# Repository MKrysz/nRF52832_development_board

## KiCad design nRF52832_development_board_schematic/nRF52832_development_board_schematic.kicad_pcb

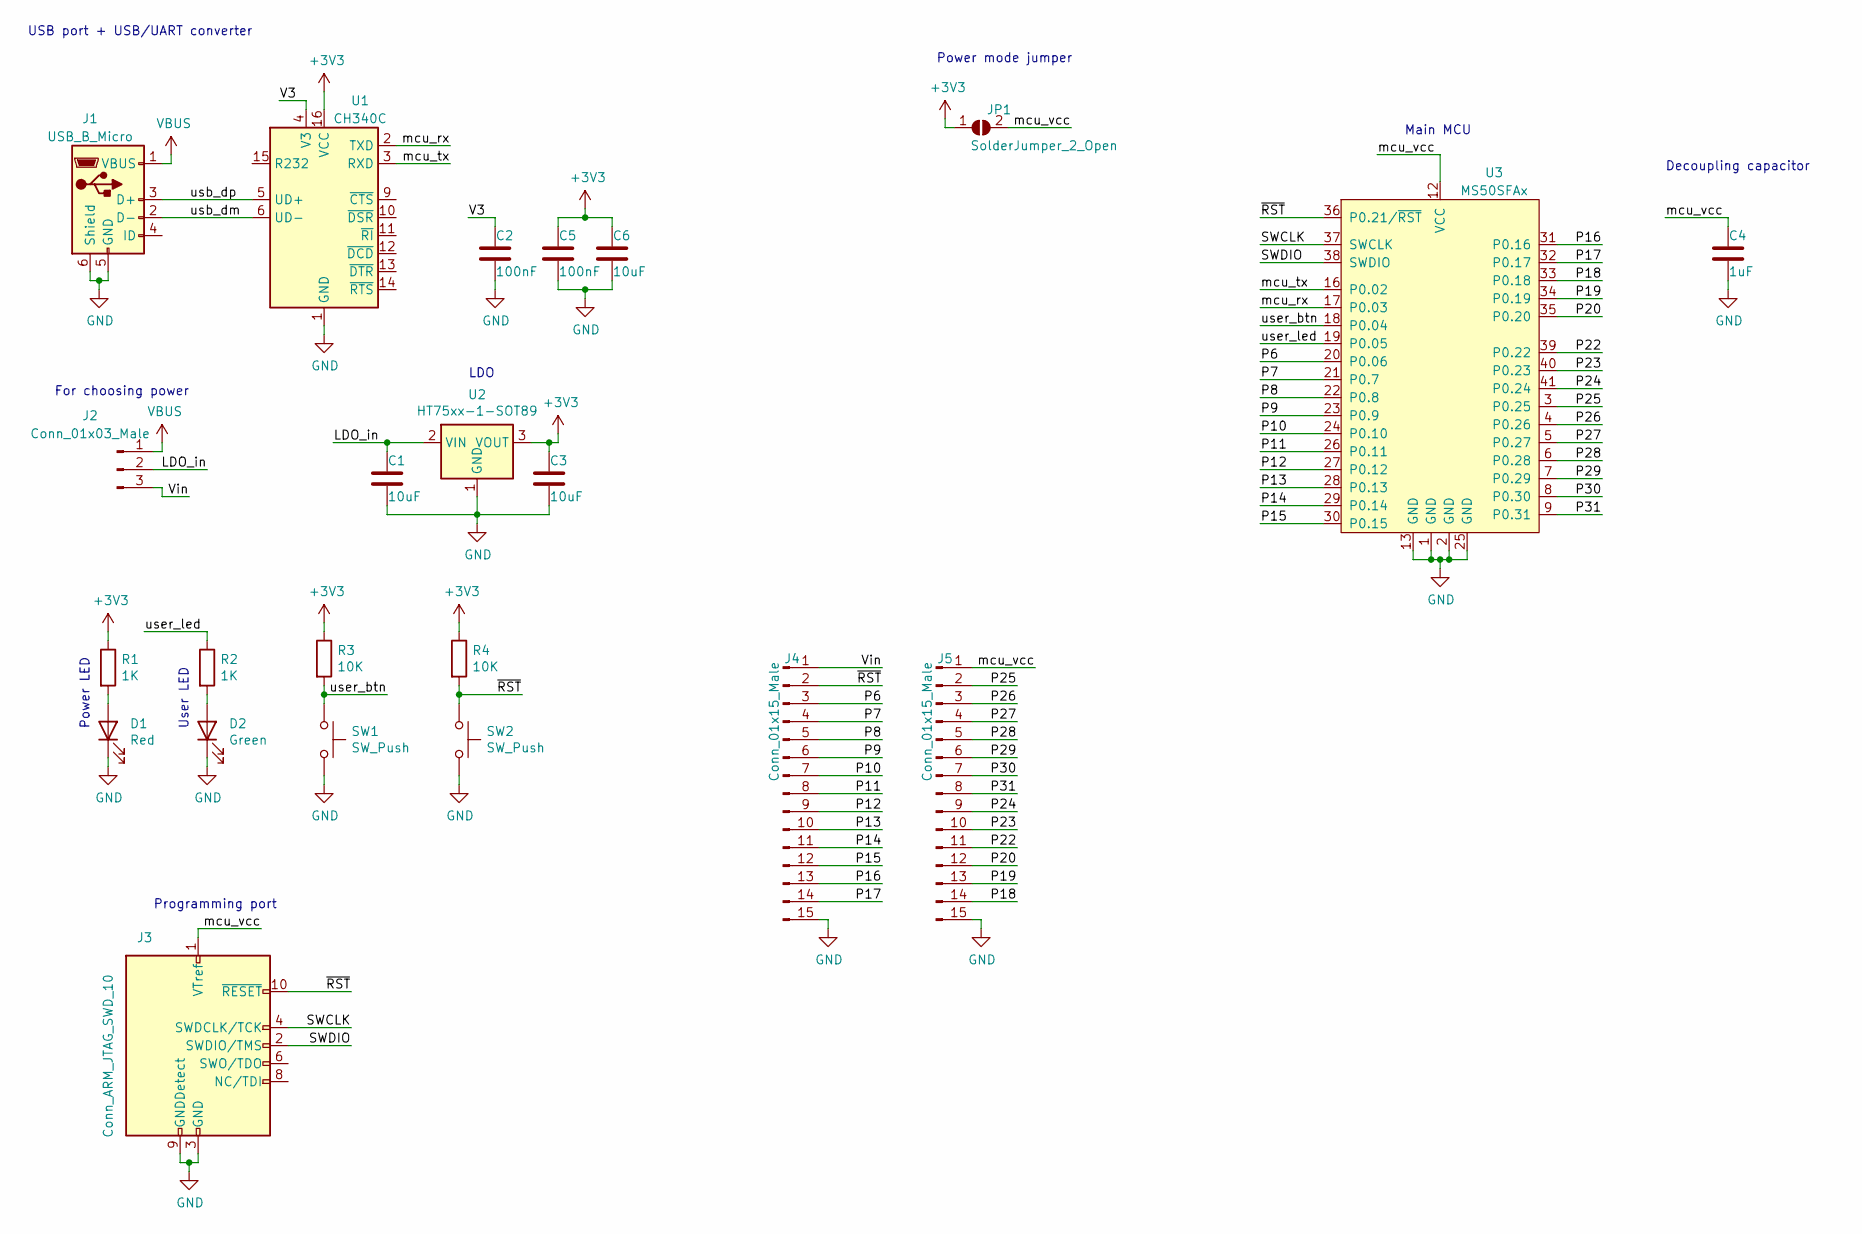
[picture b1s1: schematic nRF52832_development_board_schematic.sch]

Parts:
C1, C3, C6: 10uF; C_1206_3216Metric_Pad1.33x1.80mm_HandSolder
C2, C5: 100nF; C_1206_3216Metric_Pad1.33x1.80mm_HandSolder
C4: 1uF; C_1206_3216Metric_Pad1.33x1.80mm_HandSolder
D1: Red; LED_1206_3216Metric_Pad1.42x1.75mm_HandSolder
D2: Green; LED_1206_3216Metric_Pad1.42x1.75mm_HandSolder
J1: USB_B_Micro; USB_Micro-AB_Molex_47590-0001
J2: Conn_01x03_Male; PinHeader_1x03_P2.54mm_Vertical
J3: Conn_ARM_JTAG_SWD_10; IDC-Header_2x05_P2.54mm_Vertical
J4, J5: Conn_01x15_Male; PinHeader_1x15_P2.54mm_Vertical
JP1: SolderJumper_2_Open; SolderJumper-2_P1.3mm_Open_RoundedPad1.0x1.5mm
R1, R2: 1K; R_1206_3216Metric_Pad1.30x1.75mm_HandSolder
R3, R4: 10K; R_1206_3216Metric_Pad1.30x1.75mm_HandSolder
SW1, SW2: SW_Push; TSB008
U1: CH340C; SOIC-16_3.9x9.9mm_P1.27mm
U2: HT75xx-1-SOT89; SOT-89-3
U3: MS50SFAx; MS50SFB

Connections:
+3V3: C3.1, C5.1, C6.1, JP1.1 (A), R1.1, R3.1, R4.1, U1.16 (VCC), U2.3 (VOUT)
/LDO_in: C1.1, J2.2, U2.2 (VIN)
/P6: J4.3, U3.20 (P0.06)
/P7: J4.4, U3.21 (P0.7)
/P8: J4.5, U3.22 (P0.8)
/P9: J4.6, U3.23 (P0.9)
/P10: J4.7, U3.24 (P0.10)
/P11: J4.8, U3.26 (P0.11)
/P12: J4.9, U3.27 (P0.12)
/P13: J4.10, U3.28 (P0.13)
/P14: J4.11, U3.29 (P0.14)
/P15: J4.12, U3.30 (P0.15)
/P16: J4.13, U3.31 (P0.16)
/P17: J4.14, U3.32 (P0.17)
/P18: J5.14, U3.33 (P0.18)
/P19: J5.13, U3.34 (P0.19)
/P20: J5.12, U3.35 (P0.20)
/P22: J5.11, U3.39 (P0.22)
/P23: J5.10, U3.40 (P0.23)
/P24: J5.9, U3.41 (P0.24)
/P25: J5.2, U3.3 (P0.25)
/P26: J5.3, U3.4 (P0.26)
/P27: J5.4, U3.5 (P0.27)
/P28: J5.5, U3.6 (P0.28)
/P29: J5.6, U3.7 (P0.29)
/P30: J5.7, U3.8 (P0.30)
/P31: J5.8, U3.9 (P0.31)
/SWCLK: J3.4 (SWDCLK/TCK), U3.37 (SWCLK)
/SWDIO: J3.2 (SWDIO/TMS), U3.38 (SWDIO)
/V3: C2.1, U1.4 (V3)
/Vin: J2.3, J4.1
/mcu_rx: U1.2 (TXD), U3.17 (P0.03)
/mcu_tx: U1.3 (RXD), U3.16 (P0.02)
/mcu_vcc: C4.1, J3.1 (VTref), J5.1, JP1.2 (B), U3.12 (VCC)
/usb_dm: J1.2 (D-), U1.6 (UD-)
/usb_dp: J1.3 (D+), U1.5 (UD+)
/user_btn: R3.2, SW1.1, U3.18 (P0.04)
/user_led: R2.1, U3.19 (P0.05)
/~RST: J3.10 (~RESET~), J4.2, R4.2, SW2.1, U3.36 (P0.21/~RST)
GND: C1.2, C2.2, C3.2, C4.2, C5.2, C6.2, D1.1 (K), D2.1 (K), J1.5 (GND), J1.6 (Shield), J3.3 (GND), J3.5 (GND), J3.9 (GNDDetect), J4.15, J5.15, SW1.2, SW2.2, U1.1 (GND), U2.1 (GND), U3.1 (GND), U3.2 (GND), U3.13 (GND), U3.25 (GND)
unnamed: D1.2 (A), R1.2
unnamed: D2.2 (A), R2.2
VBUS: J1.1 (VBUS), J2.1

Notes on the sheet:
Main MCU
Decoupling capacitor
For choosing power
Power mode jumper
LDO
USB port + USB/UART converter
Power LED
User LED
Programming port

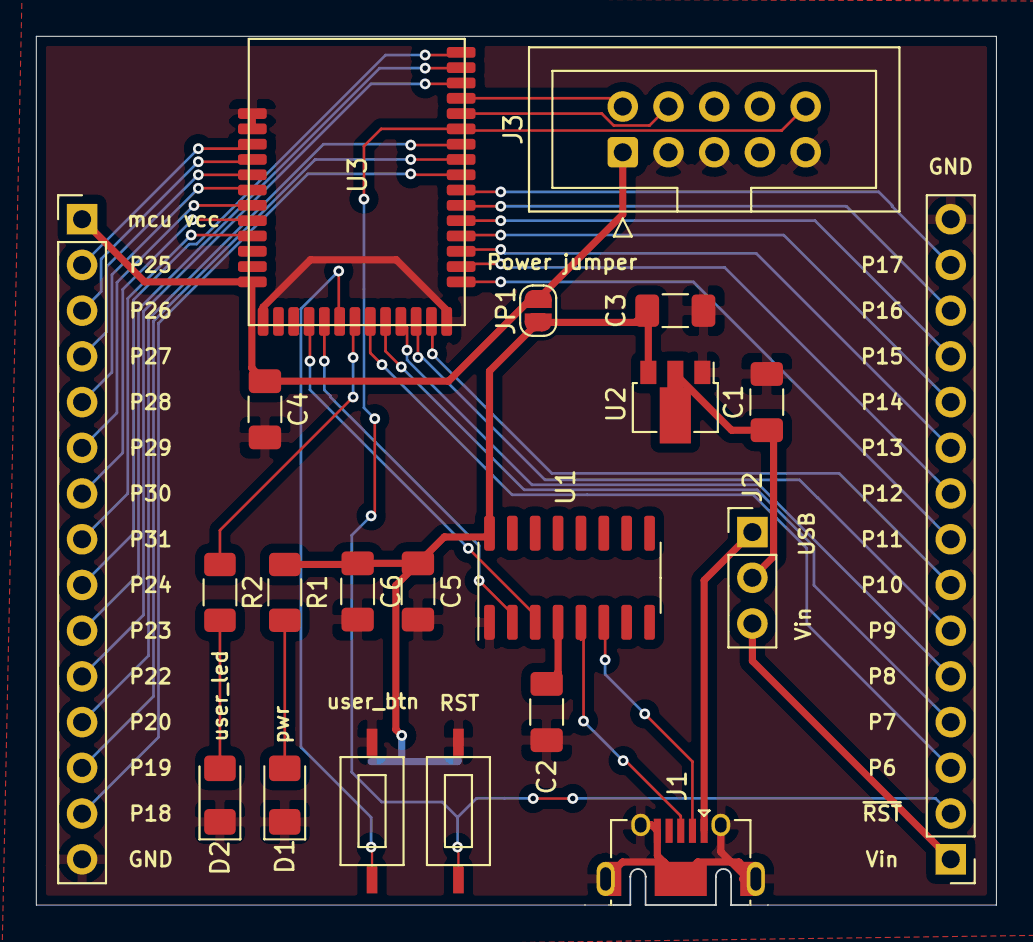
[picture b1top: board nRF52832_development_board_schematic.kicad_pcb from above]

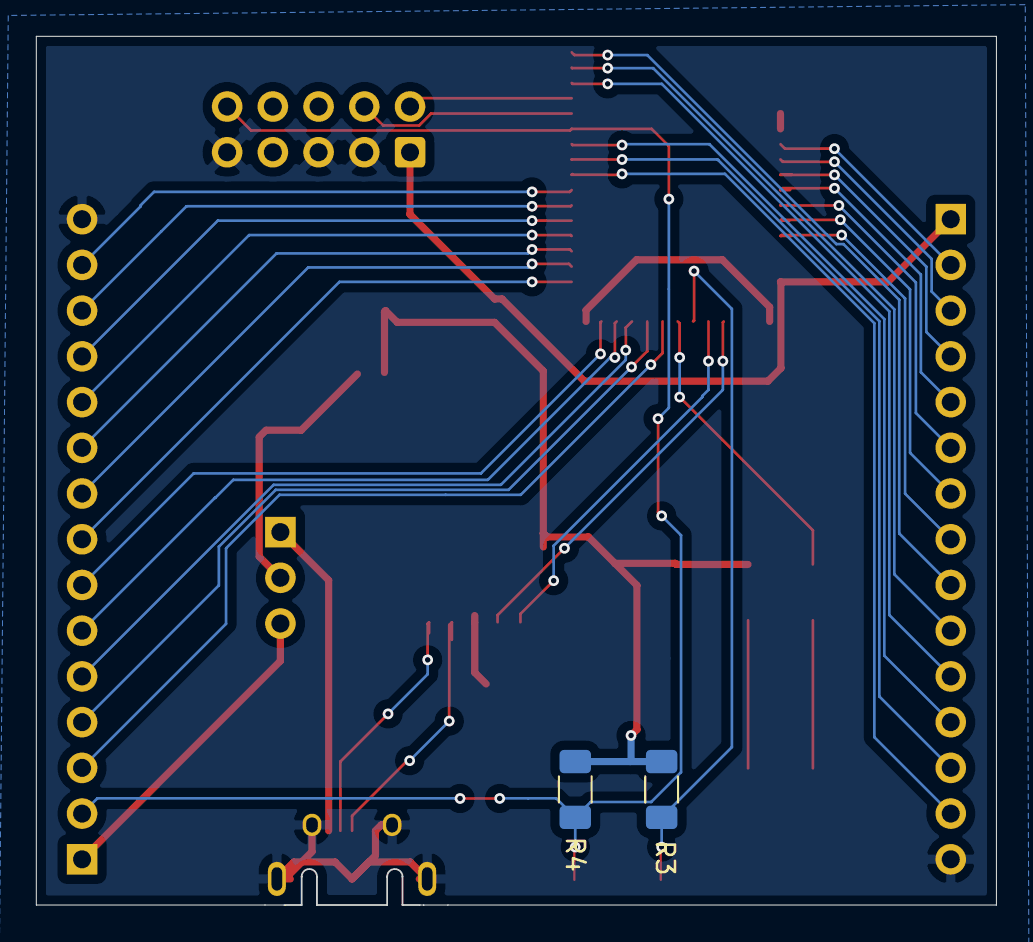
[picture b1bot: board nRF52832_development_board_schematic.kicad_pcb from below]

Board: 4 copper layers, 53.3 x 48.3 mm, 23 parts (2 on the bottom side), 43 nets.

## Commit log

2021-12-04 Version v01
